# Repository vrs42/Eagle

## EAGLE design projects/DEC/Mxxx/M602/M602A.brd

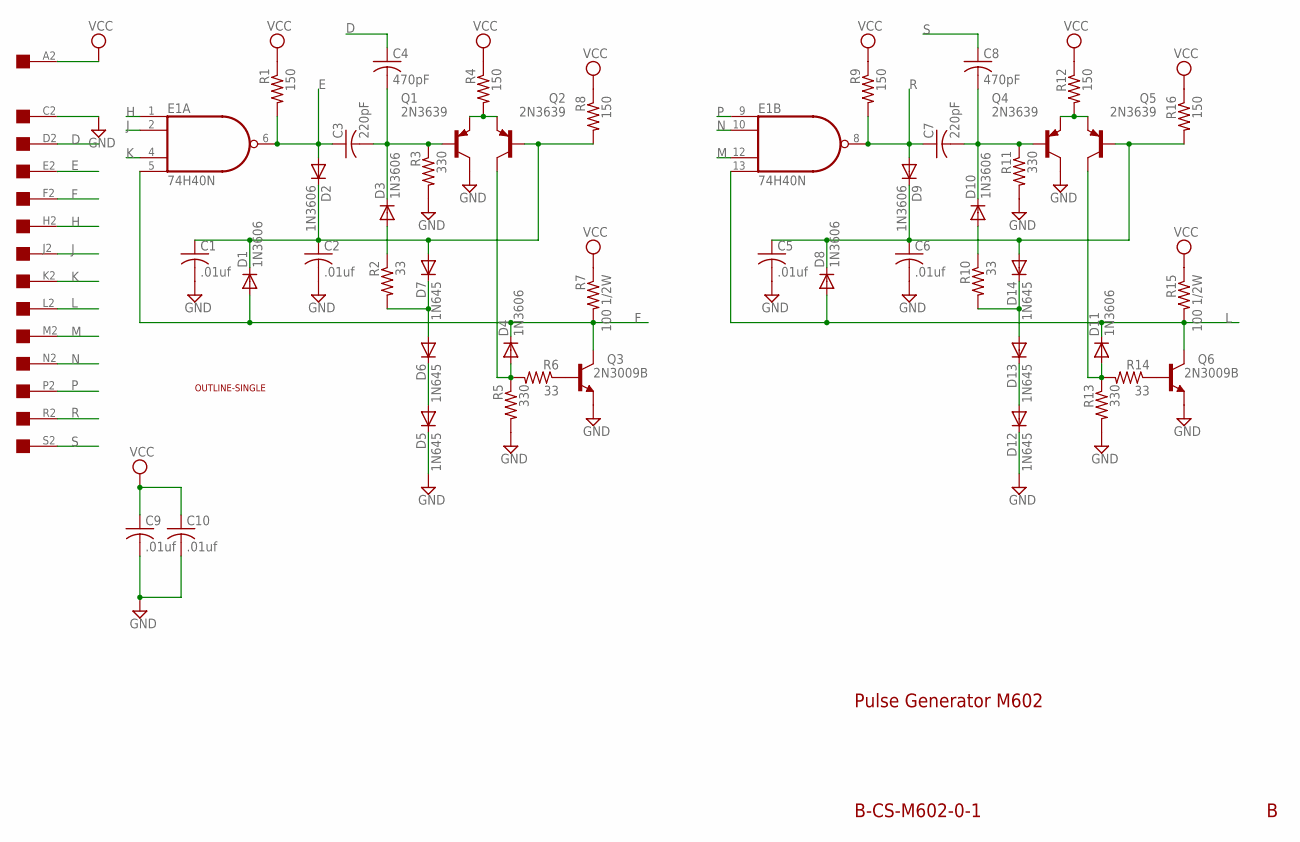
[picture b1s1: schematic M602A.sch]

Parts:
C1, C2, C5, C6, C10: .01uf; C075-032X103
C3, C7: 220pF; C150-054X183
C4, C8: 470pF; C150-054X183
C9: .01uf; C050-025X075
D1, D2, D3, D4, D8, D9, D10, D11: 1N3606; DO41-10
D5, D6, D7, D12, D13, D14: 1N645; DO41-10
E1: 74H40N; DIL14
Q1, Q2, Q4, Q5: 2N3639; TO39
Q3, Q6: 2N3009B; TO39
R1, R4, R8, R9, R12, R16: 150; 0207/10
R2, R6, R10, R14: 33; 0207/10
R3, R5, R11, R13: 330; 0207/10
R7, R15: 100 1/2W; 0309/12
U$1: EDGE-1; EDGE-CON1
U$2: OUTLINE-SINGLE; SINGLE

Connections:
D: C4.1, U$1.D2
E: C3.1, D2.A, E1.6 (O), R1.2, U$1.E2
F: D1.A, D4.C, E1.5 (I3), Q3.3 (C), R7.2, U$1.F2
GND: C1.2, C2.2, C5.2, C6.2, C9.2, C10.2, D5.C, D12.C, E1.7 (GND), Q1.3 (C), Q3.1 (E), Q4.3 (C), Q6.1 (E), R3.2, R5.2, R11.2, R13.2, U$1.C2
H: E1.1 (I0), U$1.H2
J: E1.2 (I1), U$1.J2
K: E1.4 (I2), U$1.K2
L: D8.A, D11.C, E1.13 (I3), Q6.3 (C), R15.2, U$1.L2
M: E1.12 (I2), U$1.M2
N: E1.10 (I1), U$1.N2
unnamed: C1.1, C2.1, D1.C, D2.C, D7.A, Q2.2 (B), R8.2
unnamed: D3.A, R2.1
unnamed: D10.A, R10.1
unnamed: C3.2, C4.2, D3.C, Q1.2 (B), R3.1
unnamed: Q1.1 (E), Q2.1 (E), R4.2
unnamed: D4.A, Q2.3 (C), R5.1, R6.2
unnamed: Q3.2 (B), R6.1
unnamed: D6.A, D7.C, R2.2
unnamed: D5.A, D6.C
unnamed: C7.2, C8.2, D10.C, Q4.2 (B), R11.1
unnamed: C5.1, C6.1, D8.C, D9.C, D14.A, Q5.2 (B), R16.2
unnamed: D13.A, D14.C, R10.2
unnamed: D12.A, D13.C
unnamed: Q6.2 (B), R14.1
unnamed: Q4.1 (E), Q5.1 (E), R12.2
unnamed: D11.A, Q5.3 (C), R13.1, R14.2
P: E1.9 (I0), U$1.P2
R: C7.1, D9.A, E1.8 (O), R9.2, U$1.R2
S: C8.1, U$1.S2
VCC: C9.1, C10.1, E1.14 (VCC), R1.1, R4.1, R7.1, R8.1, R9.1, R12.1, R15.1, R16.1, U$1.A2

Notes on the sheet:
Pulse Generator M602
B-CS-M602-0-1

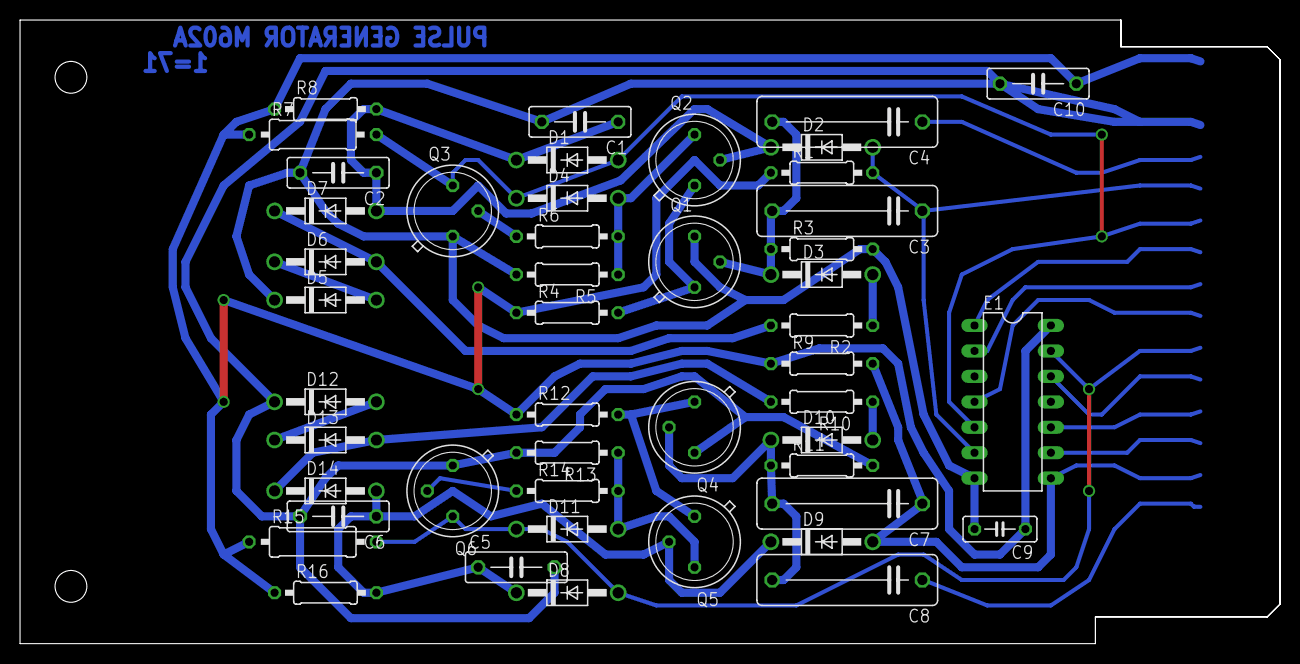
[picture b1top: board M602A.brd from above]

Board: 2 copper layers, 125.7 x 62.2 mm, 49 parts (0 on the bottom side), 30 nets.

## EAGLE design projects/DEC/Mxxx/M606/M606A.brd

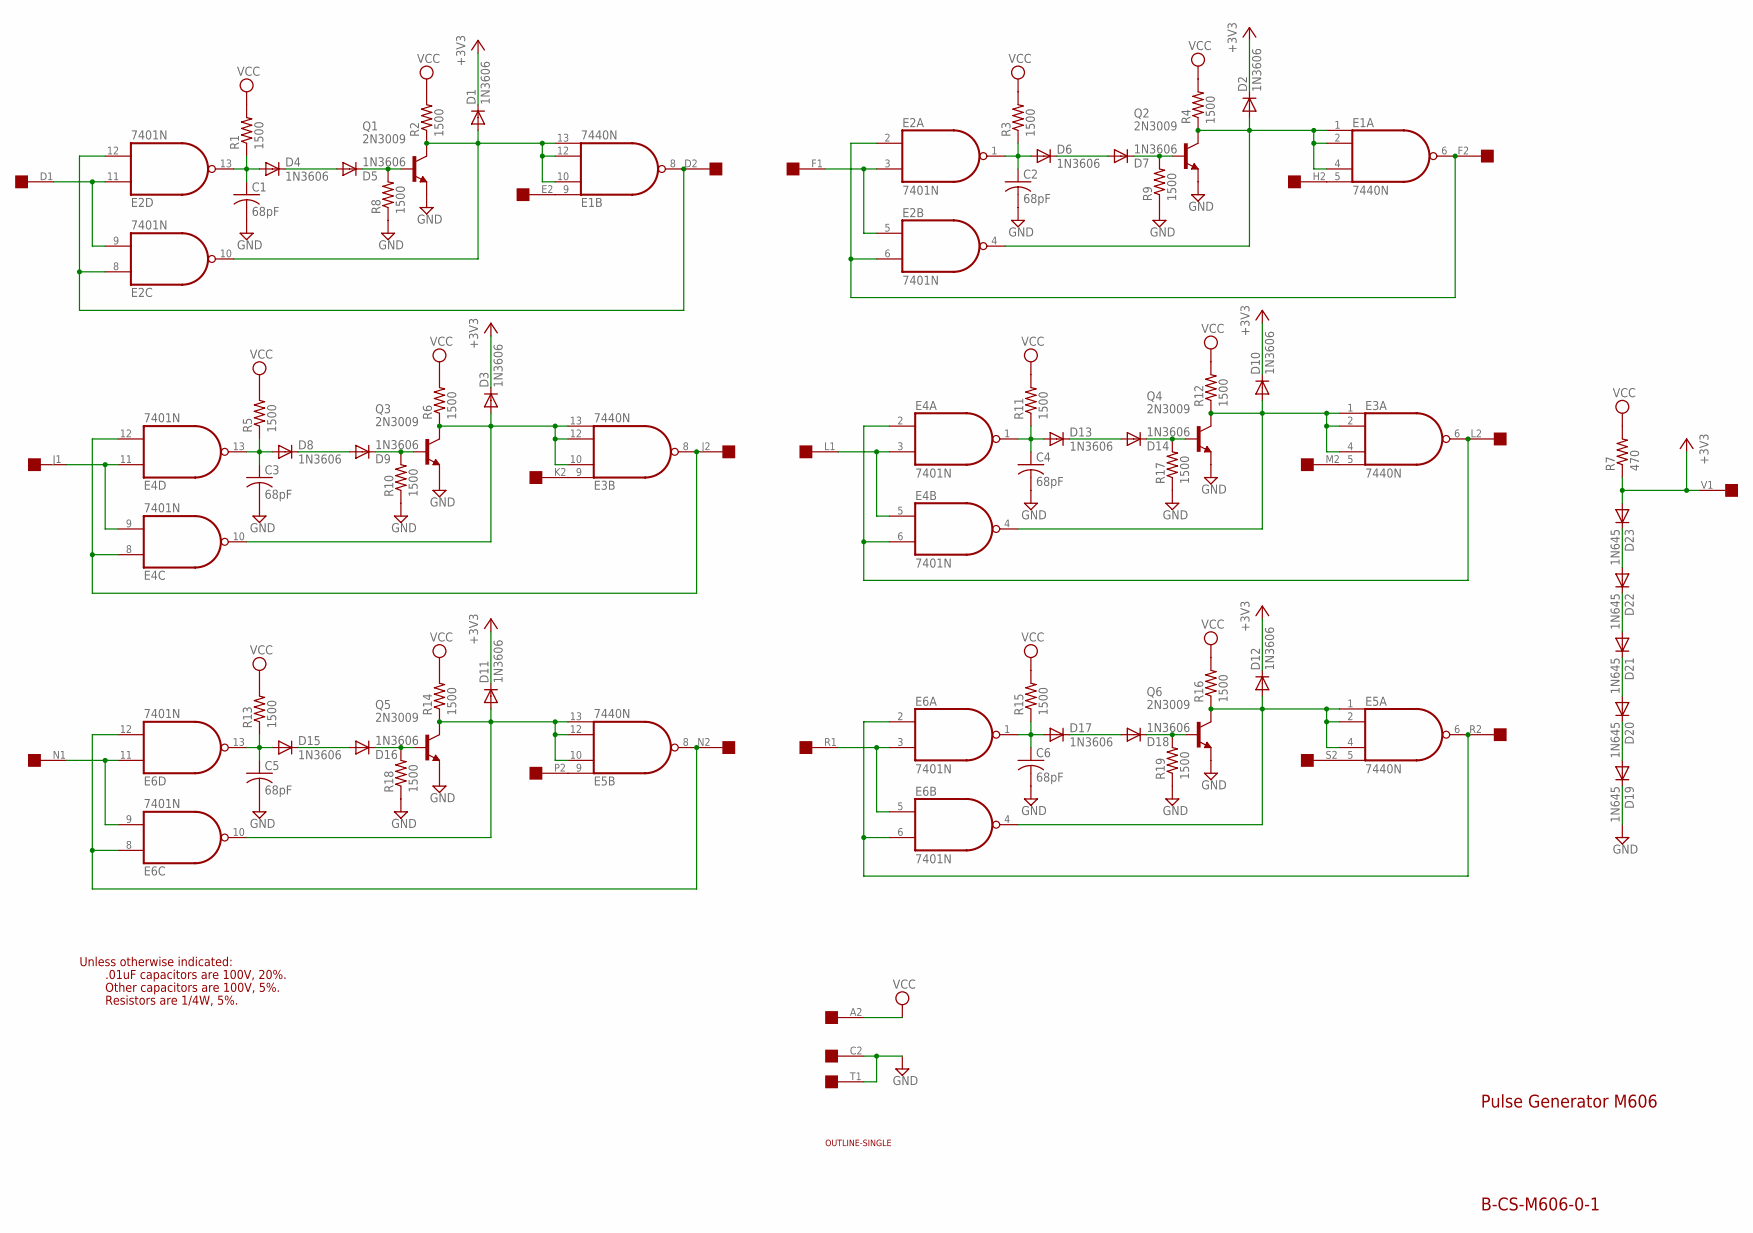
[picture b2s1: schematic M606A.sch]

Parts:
C1, C2, C3, C4, C5, C6: 68pF; C075-032X103
D1, D2, D3, D4, D5, D6, D7, D8, D9, D10, D11, D12, D13, D14, D15, D16, D17, D18: 1N3606; DO35-10
D19, D20, D21, D22, D23: 1N645; DO35-10
E1, E3, E5: 7440N; DIL14
E2, E4, E6: 7401N; DIL14
Q1, Q2, Q3, Q4, Q5, Q6: 2N3009; TO39
R1, R2, R3, R4, R5, R6, R8, R9, R10, R11, R12, R13, R14, R15, R16, R17, R18, R19: 1500; 0207/10
R7: 470; 0207/10
U$2: SINGLE; EDGE-CON2
U$4: OUTLINE-SINGLE; SINGLE

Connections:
+3V3: D1.C, D2.C, D3.C, D10.C, D11.C, D12.C, D23.A, R7.1, U$2.V1
GND: C1.2, C2.2, C3.2, C4.2, C5.2, C6.2, D19.C, E1.7 (GND), E2.7 (GND), E3.7 (GND), E4.7 (GND), E5.7 (GND), E6.7 (GND), Q1.1 (E), Q2.1 (E), Q3.1 (E), Q4.1 (E), Q5.1 (E), Q6.1 (E), R8.1, R9.1, R10.1, R17.1, R18.1, R19.1, U$2.C2, U$2.T1
unnamed: D4.C, D5.A
unnamed: D1.A, E1.10 (I1), E1.12 (I2), E1.13 (I3), E2.10 (O), Q1.3 (C), R2.1
unnamed: D5.C, Q1.2 (B), R8.2
unnamed: D6.C, D7.A
unnamed: D8.C, D9.A
unnamed: E1.9 (I0), U$2.E2
unnamed: E1.8 (O), E2.8 (I0), E2.12 (I1), U$2.D2
unnamed: E2.9 (I1), E2.11 (I0), U$2.D1
unnamed: C1.1, D4.A, E2.13 (O), R1.1
unnamed: D15.C, D16.A
unnamed: E2.3 (I1), E2.5 (I0), U$2.F1
unnamed: C2.1, D6.A, E2.1 (O), R3.1
unnamed: D7.C, Q2.2 (B), R9.2
unnamed: D2.A, E1.1 (I0), E1.2 (I1), E1.4 (I2), E2.4 (O), Q2.3 (C), R4.1
unnamed: E6.9 (I1), E6.11 (I0), U$2.N1
unnamed: E4.9 (I1), E4.11 (I0), U$2.J1
unnamed: C3.1, D8.A, E4.13 (O), R5.1
unnamed: D9.C, Q3.2 (B), R10.2
unnamed: D3.A, E3.10 (I1), E3.12 (I2), E3.13 (I3), E4.10 (O), Q3.3 (C), R6.1
unnamed: D13.C, D14.A
unnamed: E4.3 (I1), E4.5 (I0), U$2.L1
unnamed: C4.1, D13.A, E4.1 (O), R11.1
unnamed: D14.C, Q4.2 (B), R17.2
unnamed: D10.A, E3.1 (I0), E3.2 (I1), E3.4 (I2), E4.4 (O), Q4.3 (C), R12.1
unnamed: C5.1, D15.A, E6.13 (O), R13.1
unnamed: D16.C, Q5.2 (B), R18.2
unnamed: D11.A, E5.10 (I1), E5.12 (I2), E5.13 (I3), E6.10 (O), Q5.3 (C), R14.1
unnamed: D17.C, D18.A
unnamed: E6.3 (I1), E6.5 (I0), U$2.R1
unnamed: C6.1, D17.A, E6.1 (O), R15.1
unnamed: D18.C, Q6.2 (B), R19.2
unnamed: D12.A, E5.1 (I0), E5.2 (I1), E5.4 (I2), E6.4 (O), Q6.3 (C), R16.1
unnamed: E1.5 (I3), U$2.H2
unnamed: E1.6 (O), E2.2 (I0), E2.6 (I1), U$2.F2
unnamed: E3.8 (O), E4.8 (I0), E4.12 (I1), U$2.J2
unnamed: E3.9 (I0), U$2.K2
unnamed: E3.6 (O), E4.2 (I0), E4.6 (I1), U$2.L2
unnamed: E3.5 (I3), U$2.M2
unnamed: E5.8 (O), E6.8 (I0), E6.12 (I1), U$2.N2
unnamed: E5.9 (I0), U$2.P2
unnamed: E5.6 (O), E6.2 (I0), E6.6 (I1), U$2.R2
unnamed: E5.5 (I3), U$2.S2
unnamed: D22.A, D23.C
unnamed: D21.A, D22.C
unnamed: D19.A, D20.C
unnamed: D20.A, D21.C
VCC: E1.14 (VCC), E2.14 (VCC), E3.14 (VCC), E4.14 (VCC), E5.14 (VCC), E6.14 (VCC), R1.2, R2.2, R3.2, R4.2, R5.2, R6.2, R7.2, R11.2, R12.2, R13.2, R14.2, R15.2, R16.2, U$2.A2

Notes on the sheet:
Pulse Generator M606
B-CS-M606-0-1
Unless otherwise indicated:
.01uF capacitors are 100V, 20%.
Other capacitors are 100V, 5%.
Resistors are 1/4W, 5%.

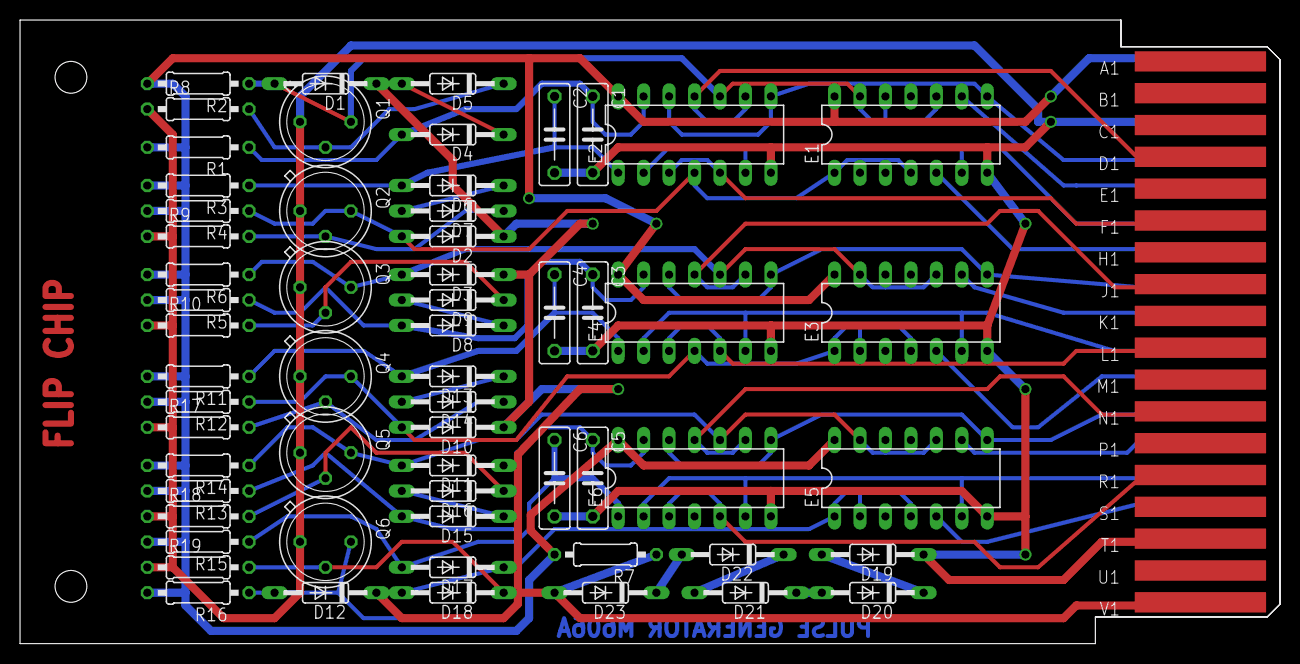
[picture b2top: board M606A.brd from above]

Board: 2 copper layers, 125.7 x 62.2 mm, 63 parts (0 on the bottom side), 49 nets.

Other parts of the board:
U$1: FLIPCHIP

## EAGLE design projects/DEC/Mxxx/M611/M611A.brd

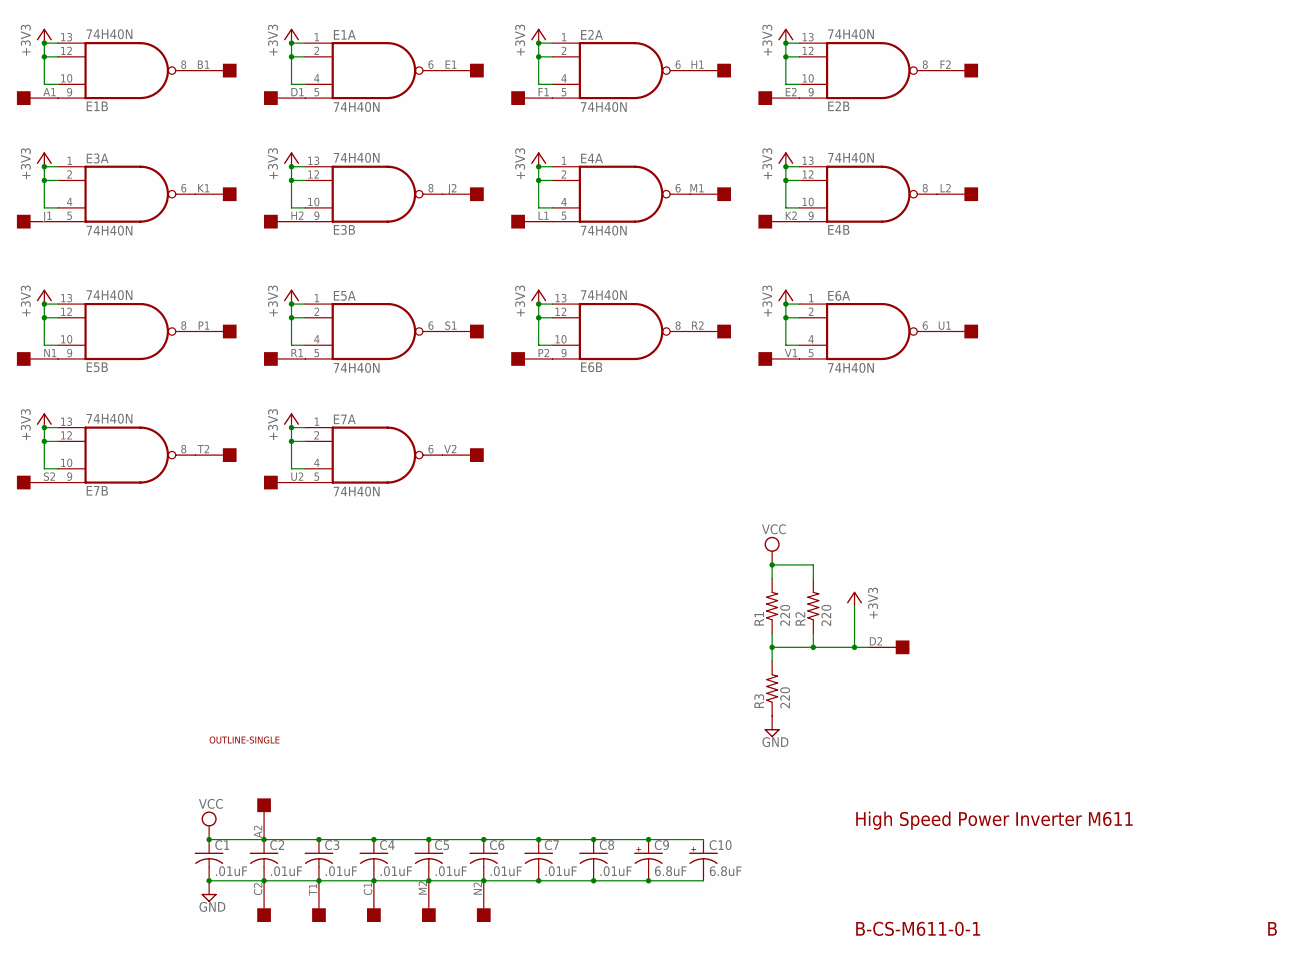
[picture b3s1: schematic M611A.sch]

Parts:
C1, C2, C3, C4, C5, C6, C7, C8: .01uF; C050-025X075
C9, C10: 6.8uF; E12-8
E1, E2, E3, E4, E5, E6, E7: 74H40N; DIL14
R1, R2, R3: 220; 0207/10
U$1: SINGLE; EDGE-CON2
U$4: OUTLINE-SINGLE; SINGLE

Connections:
+3V3: E1.1 (I0), E1.2 (I1), E1.4 (I2), E1.10 (I1), E1.12 (I2), E1.13 (I3), E2.1 (I0), E2.2 (I1), E2.4 (I2), E2.10 (I1), E2.12 (I2), E2.13 (I3), E3.1 (I0), E3.2 (I1), E3.4 (I2), E3.10 (I1), E3.12 (I2), E3.13 (I3), E4.1 (I0), E4.2 (I1), E4.4 (I2), E4.10 (I1), E4.12 (I2), E4.13 (I3), E5.1 (I0), E5.2 (I1), E5.4 (I2), E5.10 (I1), E5.12 (I2), E5.13 (I3), E6.1 (I0), E6.2 (I1), E6.4 (I2), E6.10 (I1), E6.12 (I2), E6.13 (I3), E7.1 (I0), E7.2 (I1), E7.4 (I2), E7.10 (I1), E7.12 (I2), E7.13 (I3), R1.1, R2.1, R3.2, U$1.D2
GND: C1.2, C2.2, C3.2, C4.2, C5.2, C6.2, C7.2, C8.2, C9.-, C10.-, E1.7 (GND), E2.7 (GND), E3.7 (GND), E4.7 (GND), E5.7 (GND), E6.7 (GND), E7.7 (GND), R3.1, U$1.C1, U$1.C2, U$1.M2, U$1.N2, U$1.T1
unnamed: E1.9 (I0), U$1.A1
unnamed: E1.8 (O), U$1.B1
unnamed: E1.5 (I3), U$1.D1
unnamed: E1.6 (O), U$1.E1
unnamed: E2.6 (O), U$1.H1
unnamed: E2.5 (I3), U$1.F1
unnamed: E3.5 (I3), U$1.J1
unnamed: E3.6 (O), U$1.K1
unnamed: E2.9 (I0), U$1.E2
unnamed: E2.8 (O), U$1.F2
unnamed: E3.9 (I0), U$1.H2
unnamed: E3.8 (O), U$1.J2
unnamed: E4.5 (I3), U$1.L1
unnamed: E4.6 (O), U$1.M1
unnamed: E4.9 (I0), U$1.K2
unnamed: E4.8 (O), U$1.L2
unnamed: E5.9 (I0), U$1.N1
unnamed: E5.8 (O), U$1.P1
unnamed: E5.5 (I3), U$1.R1
unnamed: E5.6 (O), U$1.S1
unnamed: E6.9 (I0), U$1.P2
unnamed: E6.8 (O), U$1.R2
unnamed: E6.5 (I3), U$1.V1
unnamed: E6.6 (O), U$1.U1
unnamed: E7.9 (I0), U$1.S2
unnamed: E7.8 (O), U$1.T2
unnamed: E7.5 (I3), U$1.U2
unnamed: E7.6 (O), U$1.V2
VCC: C1.1, C2.1, C3.1, C4.1, C5.1, C6.1, C7.1, C8.1, C9.+, C10.+, E1.14 (VCC), E2.14 (VCC), E3.14 (VCC), E4.14 (VCC), E5.14 (VCC), E6.14 (VCC), E7.14 (VCC), R1.2, R2.2, U$1.A2

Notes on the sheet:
High Speed Power Inverter M611
B-CS-M611-0-1

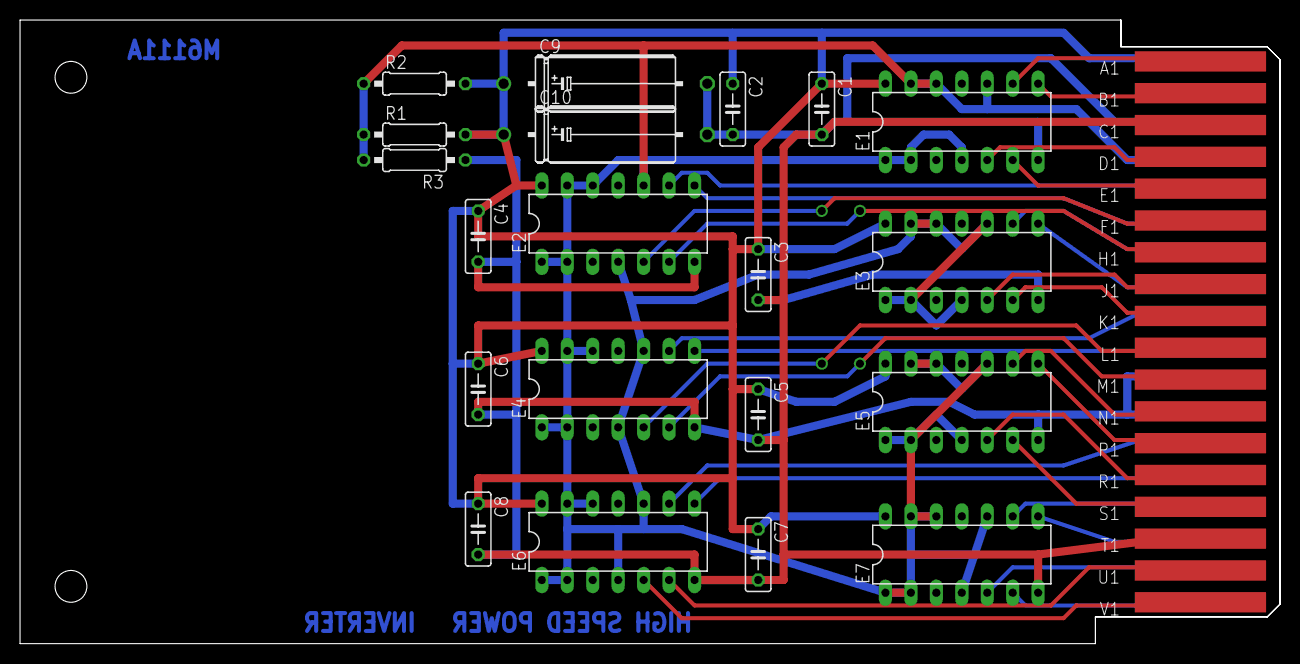
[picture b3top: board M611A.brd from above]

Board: 2 copper layers, 125.7 x 62.2 mm, 22 parts (0 on the bottom side), 31 nets.
